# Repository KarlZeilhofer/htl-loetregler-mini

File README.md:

HTL Lötregler Mini
==================

Einfacher Regler für JBC Lötspitzen der Serie T210, T245 und T470, Weller RT-Spitzen und TS100-Spitzen sollten auch funktionieren.

Vorrangig SMD-Bauteile, Größe 3216. 
Bauteilauswahl für Handbestückung ohne SMD-Schablone optimiert

Design ist möglichst kostengünstig, speziell für Schüler-Budget. 

# Merkmale:
## Controller
* ATmega328, Kompatibel zu Arduino Nano
* 5V, 16MHz
* externe 2.5V Spannungsreferenz für ADC

## Stromversorgung
* Spannungsversorgung: 15 bis 48V, Akku oder Netzteil
* Tiefentladeschutz
* 10A Schmelzsicherung
* 48V TVS-Schutzdiode
* Ein-/Aus-Taster
* Schaltregler von Vin auf 12V und 5V
* 6.3 mm Flachsteckverbinder für die direkte Kontaktierung von 18V Makita Akkus, oder Hofer ActivEnergy Akkus mit 20 oder 40V. 

## Leistungsteil
* Highside N-Kanal MOS-FET: 80V, 10mR (geringe Verlustleistung, hohe Spannungsfestigkeit)
* zugehöriger Gatetreiber: notwendig für N-Kanal MOS-FET

## Sensorik
* Messverstärker zur Temperaturmessung der Lötspitze (24 µV/K)
* Spannungsmessung der Versorgung
* Messung der Leiterplattentemperatur
* Strommessung des Heizelements über 1mR-Shunt

## Benutzerschnittstelle
* OLED Display mit 128x32 Pixel, 23mm Diagonale
* 4 Bedientaster (Rauf, Runter, Enter, Zurück)

## Kommunikation
* Arduino USB
* AVR ISP
* Wahlweise
  * RS232
  * oder RS485 zur Kommunikation mit einem Steuerbaren Netzgerät (12, 24, 48V).

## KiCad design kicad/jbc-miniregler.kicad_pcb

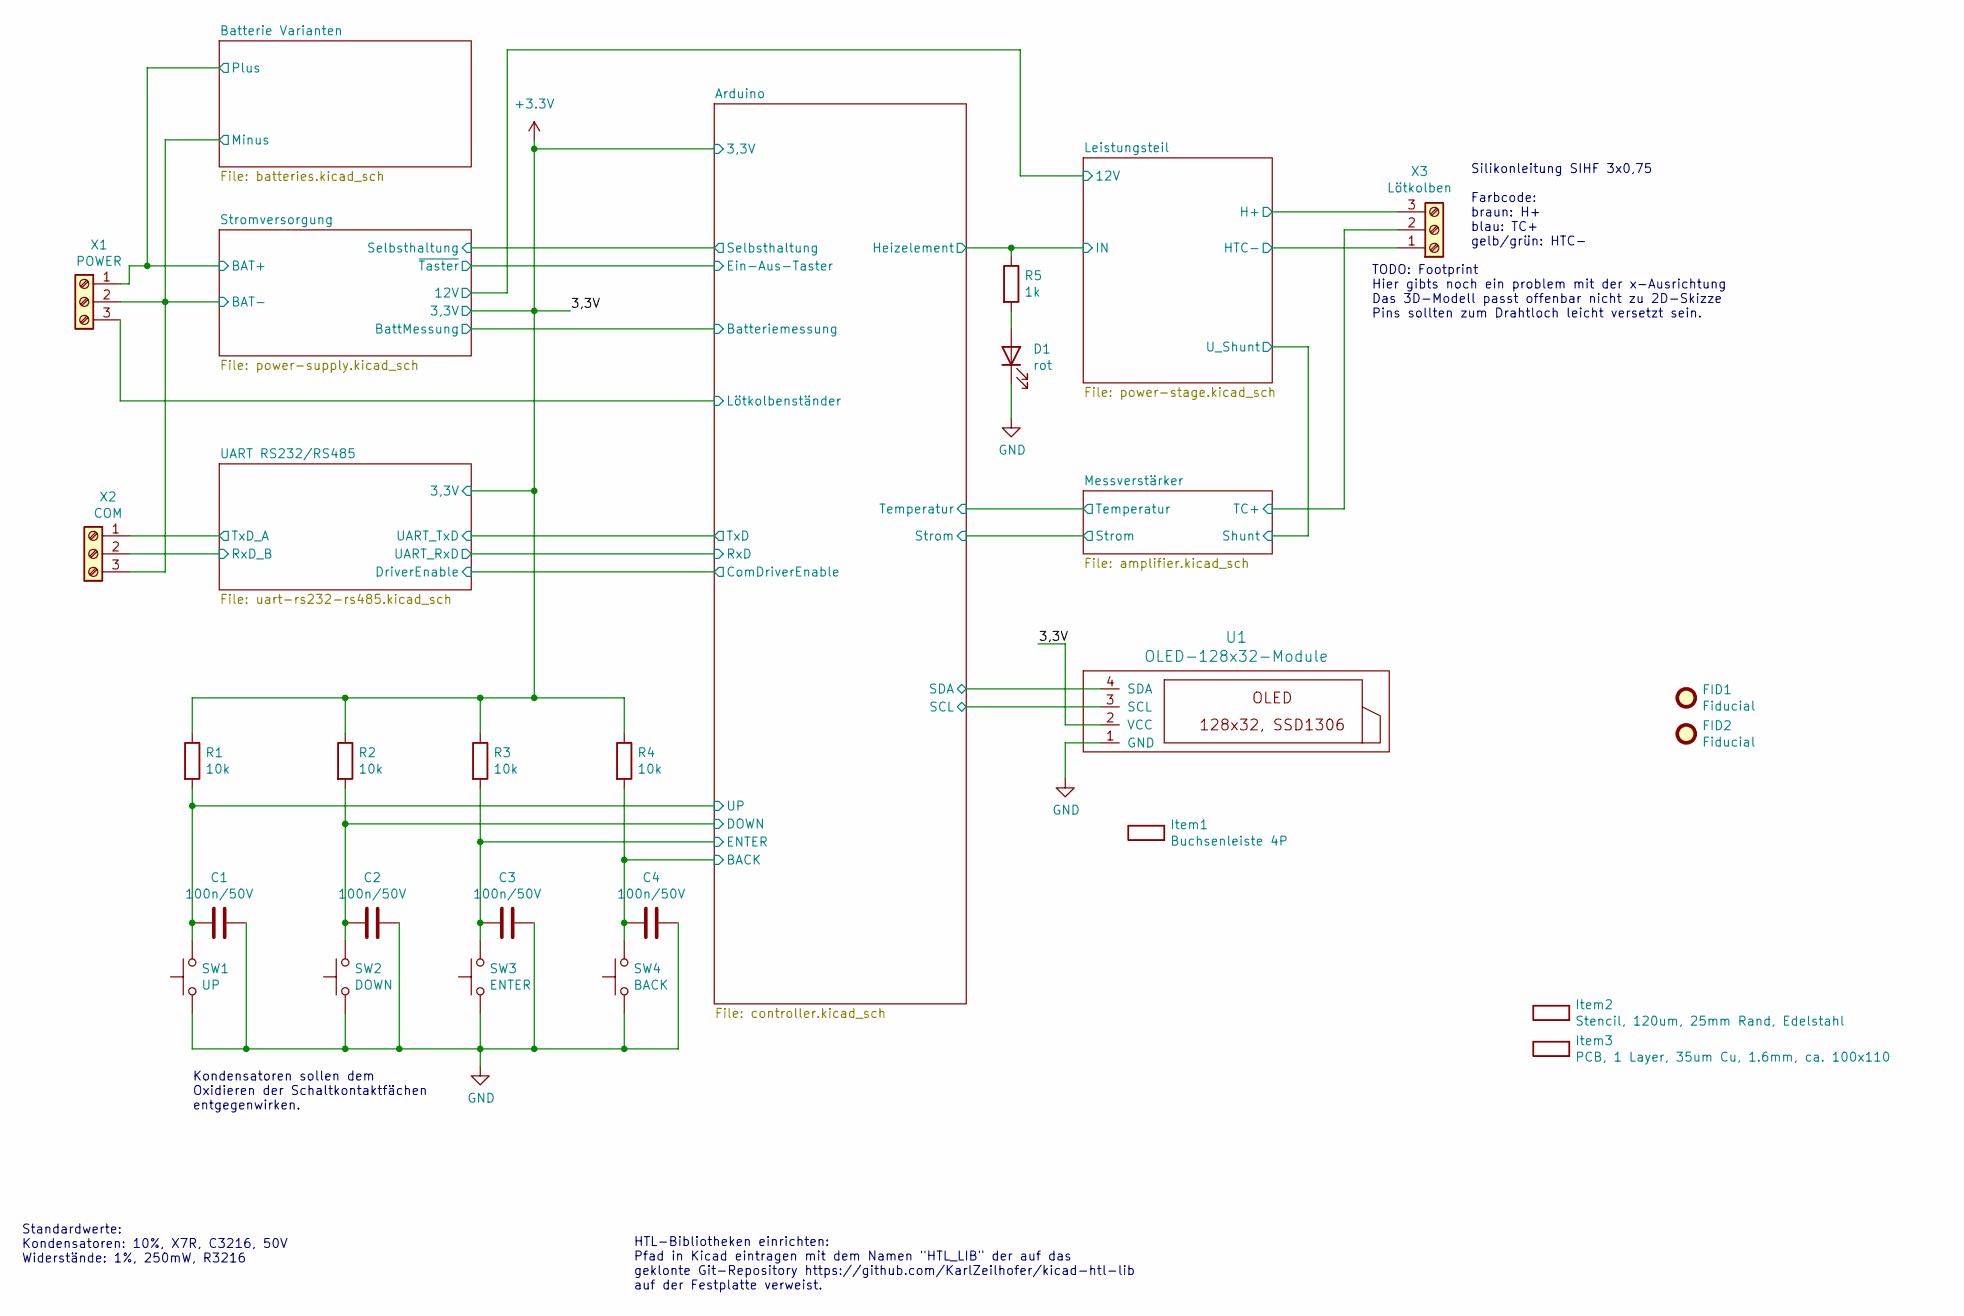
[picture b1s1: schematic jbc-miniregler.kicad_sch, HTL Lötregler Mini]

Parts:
C1, C2, C3, C4: 100n/50V; C_1206_3216Metric; ManPartNr FN31X104K500PXG
D1: rot; LED_1206_3216Metric; ManPartNr XL-3216UOC
FID1, FID2: Fiducial; paste-fiducial; ManPartNr NAP
Item1: Buchsenleiste 4P; Virtual-Item; ManPartNr A2541HWV-4P
Item2: Stencil, 120um, 25mm Rand, Edelstahl; Virtual-Item
Item3: PCB, 1 Layer, 35um Cu, 1.6mm, ca. 100x110; Virtual-Item
R1, R2, R3, R4: 10k; R_1206_3216Metric; ManPartNr RS-06K103JT
R5: 1k; R_1206_3216Metric; ManPartNr RTT03101JTP
SW1: UP; SW_Push_5.1mm_H1.5mm; ManPartNr TS-1187A-B-A-B
SW2: DOWN; SW_Push_5.1mm_H1.5mm; ManPartNr TS-1187A-B-A-B
SW3: ENTER; SW_Push_5.1mm_H1.5mm; ManPartNr TS-1187A-B-A-B
SW4: BACK; SW_Push_5.1mm_H1.5mm; ManPartNr TS-1187A-B-A-B
U1: OLED-128x32-Module; OLED-128x32
X1: POWER; Federklemme_KF142_3P_P5.08mm_C475145; ManPartNr KF142R-5.08-3P
X2: COM; Federklemme_KF142_3P_P5.08mm_C475145; ManPartNr KF142R-5.08-3P
X3: Lötkolben; Federklemme_KF142_3P_P5.08mm_C475145; ManPartNr KF142R-5.08-3P

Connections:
+3.3V: R1.1, R2.1, R3.1, R4.1, U1.2 (VCC); also elsewhere on the board
/Arduino/BACK: C4.2, R4.2, SW4.2; also elsewhere on the board
/Arduino/DOWN: C2.2, R2.2, SW2.2; also elsewhere on the board
/Arduino/ENTER: C3.2, R3.2, SW3.2; also elsewhere on the board
/Arduino/Heizelement: R5.1; also elsewhere on the board
/Arduino/Lötkolbenständer: X1.3; also elsewhere on the board
/Arduino/SCL: U1.3 (SCL); also elsewhere on the board
/Arduino/SDA: U1.4 (SDA); also elsewhere on the board
/Arduino/UP: C1.2, R1.2, SW1.2; also elsewhere on the board
/Batterie Varianten/Plus: X1.1; also elsewhere on the board
/Leistungsteil/H+: X3.3; also elsewhere on the board
/Leistungsteil/HTC-: X3.1; also elsewhere on the board
/Messverstärker/TC+: X3.2; also elsewhere on the board
/UART RS232/RS485/RxD_B: X2.2; also elsewhere on the board
/UART RS232/RS485/TxD_A: X2.1; also elsewhere on the board
GNDPWR: X1.2, X2.3; also elsewhere on the board
unnamed: D1.2 (A), R5.2

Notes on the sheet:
TODO: Footprint Hier gibts noch ein problem mit der x-Ausrichtung Das 3D-Modell passt offenbar nicht zu 2D-Skizze Pins sollten zum Drahtloch leicht versetzt sein.
Standardwerte: Kondensatoren: 10%, X7R, C3216, 50V Widerstände: 1%, 250mW, R3216
HTL-Bibliotheken einrichten: Pfad in Kicad eintragen mit dem Namen "HTL_LIB" der auf das geklonte Git-Repository https://github.com/KarlZeilhofer/kicad-htl-lib auf der Festplatte verweist.
Silikonleitung SIHF 3x0,75 Farbcode: braun: H+ blau: TC+ gelb/grün: HTC-
Kondensatoren sollen dem Oxidieren der Schaltkontaktfächen entgegenwirken.

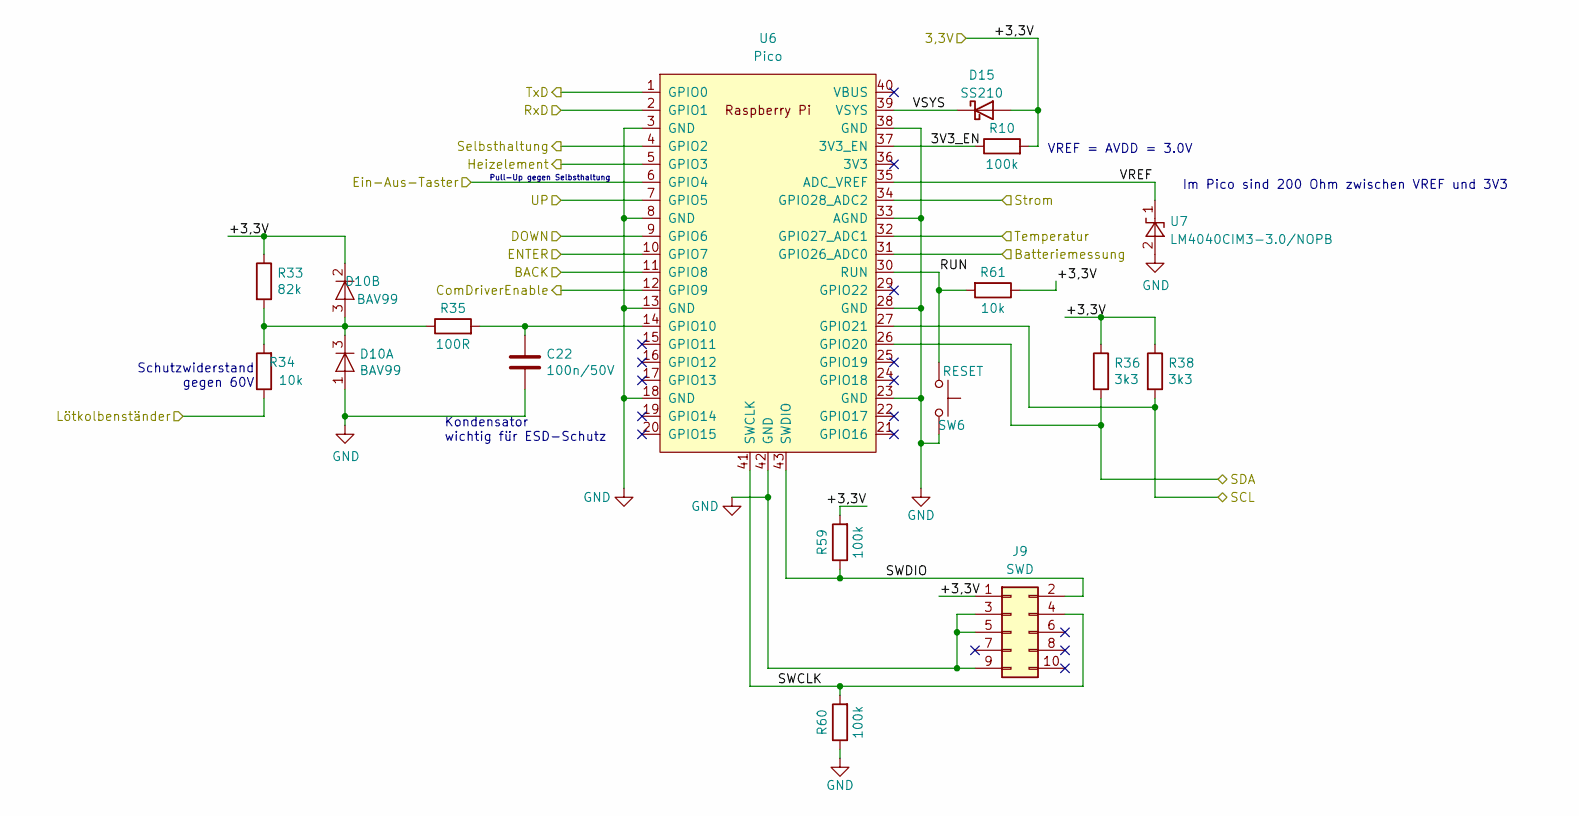
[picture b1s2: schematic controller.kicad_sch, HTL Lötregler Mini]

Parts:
C22: 100n/50V; C_1206_3216Metric; ManPartNr FN31X104K500PXG
D10: BAV99; SOT-23; ManPartNr BAV99
D15: SS210; D_SMA_wide; ManPartNr SS210A-W
J9: SWD; IDC-Header_2x05_P2.54mm_Vertical; ManPartNr C5665
R10, R59, R60: 100k; R_1206_3216Metric; ManPartNr RMC1206100K1%N
R33: 82k; R_1206_3216Metric; ManPartNr RS-06K8202FT
R34, R61: 10k; R_1206_3216Metric; ManPartNr RS-06K103JT
R35: 100R; R_1206_3216Metric; ManPartNr CR1206F100RP05Z
R36, R38: 3k3; R_1206_3216Metric; ManPartNr AC1206FR-073K3L
SW6: RESET; SW_Push_5.1mm_H1.5mm; ManPartNr TS-1187A-B-A-B
U6: Pico; RPi_Pico_SMD
U7: LM4040CIM3-3.0/NOPB; SOT-23

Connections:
+3.3V: D10.2 (K), D15.2 (A), J9.1, R10.2, R33.1, R36.1, R38.1, R59.2, R61.1; also elsewhere on the board
/Arduino/3V3_EN: R10.1, U6.37 (3V3_EN)
/Arduino/BACK: U6.11 (GPIO8); also elsewhere on the board
/Arduino/Batteriemessung: U6.31 (GPIO26_ADC0); also elsewhere on the board
/Arduino/ComDriverEnable: U6.12 (GPIO9); also elsewhere on the board
/Arduino/DOWN: U6.9 (GPIO6); also elsewhere on the board
/Arduino/ENTER: U6.10 (GPIO7); also elsewhere on the board
/Arduino/Ein-Aus-Taster: U6.6 (GPIO4); also elsewhere on the board
/Arduino/Heizelement: U6.5 (GPIO3); also elsewhere on the board
/Arduino/Lötkolbenständer: R34.1; also elsewhere on the board
/Arduino/RUN: R61.2, SW6.1, U6.30 (RUN)
/Arduino/RxD: U6.2 (GPIO1); also elsewhere on the board
/Arduino/SCL: R38.2, U6.27 (GPIO21); also elsewhere on the board
/Arduino/SDA: R36.2, U6.26 (GPIO20); also elsewhere on the board
/Arduino/SWCLK: J9.4, R60.2, U6.41 (SWCLK)
/Arduino/SWDIO: J9.2, R59.1, U6.43 (SWDIO)
/Arduino/Selbsthaltung: U6.4 (GPIO2); also elsewhere on the board
/Arduino/Strom: U6.34 (GPIO28_ADC2); also elsewhere on the board
/Arduino/Temperatur: U6.32 (GPIO27_ADC1); also elsewhere on the board
/Arduino/TxD: U6.1 (GPIO0); also elsewhere on the board
/Arduino/UP: U6.7 (GPIO5); also elsewhere on the board
/Arduino/VREF: U6.35 (ADC_VREF), U7.1 (K)
/Arduino/VSYS: D15.1 (K), U6.39 (VSYS)
unnamed: C22.1, R35.2, U6.14 (GPIO10)
unnamed: D10.3 (A), R33.2, R34.2, R35.1

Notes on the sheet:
VREF = AVDD = 3.0V
Pull-Up gegen Selbsthaltung
Im Pico sind 200 Ohm zwischen VREF und 3V3
Kondensator wichtig für ESD-Schutz
Schutzwiderstand gegen 60V

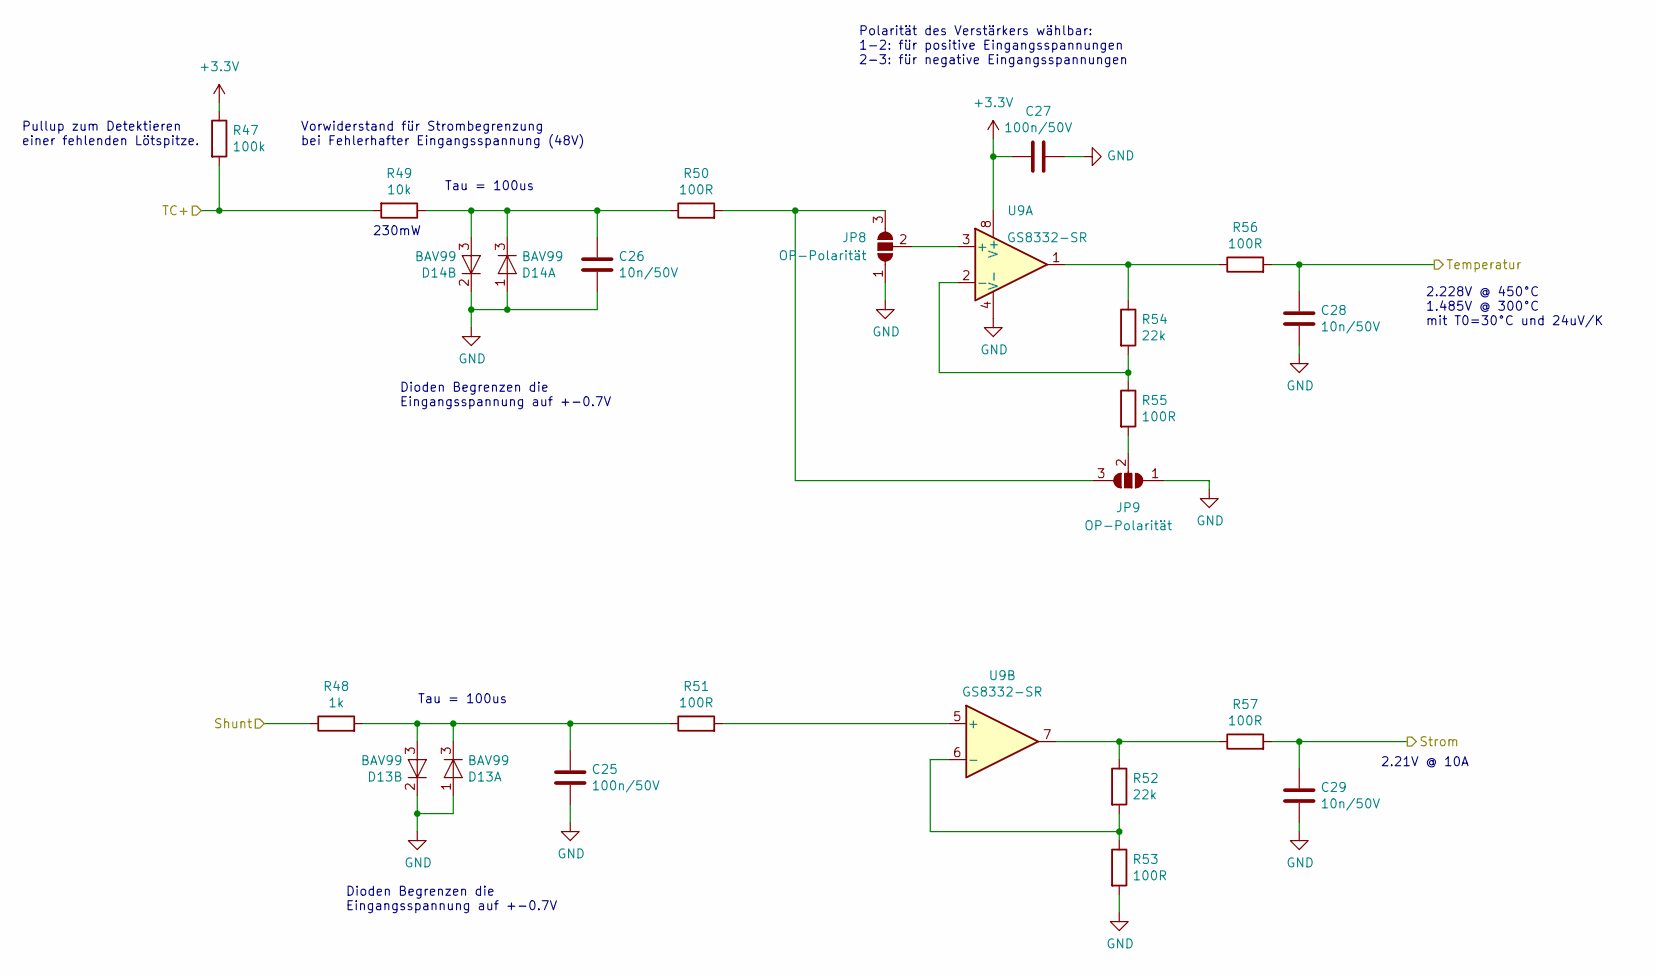
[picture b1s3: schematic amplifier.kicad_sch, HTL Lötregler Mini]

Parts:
C25, C27: 100n/50V; C_1206_3216Metric; ManPartNr FN31X104K500PXG
C26, C28, C29: 10n/50V; C_1206_3216Metric; ManPartNr FN31X103K500PXG
D13, D14: BAV99; SOT-23; ManPartNr BAV99
JP8, JP9: OP-Polarität; SolderJumper-3_P2.0mm_Open_TrianglePad1.0x1.5mm_NumberLabels; ManPartNr NAP
R47: 100k; R_1206_3216Metric; ManPartNr RMC1206100K1%N
R48: 1k; R_1206_3216Metric; ManPartNr RTT03101JTP
R49: 10k; R_1206_3216Metric; ManPartNr RS-06K103JT
R50, R51, R53, R55, R56, R57: 100R; R_1206_3216Metric; ManPartNr CR1206F100RP05Z
R52, R54: 22k; R_1206_3216Metric
U9: GS8332-SR; SOIC-8_3.9x4.9mm_P1.27mm; ManPartNr GS8332-SR

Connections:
+3.3V: C27.2, R47.1, U9.8 (V+); also elsewhere on the board
/Arduino/Strom: C29.1, R57.2; also elsewhere on the board
/Arduino/Temperatur: C28.1, R56.2; also elsewhere on the board
/Leistungsteil/U_Shunt: R48.1; also elsewhere on the board
/Messverstärker/TC+: R47.2, R49.2; also elsewhere on the board
unnamed: C25.2, D13.3 (K), R48.2, R51.1
unnamed: C26.1, D14.3 (K), R49.1, R50.1
unnamed: JP8.2 (C), U9.3 (+)
unnamed: JP8.3 (B), JP9.3 (B), R50.2
unnamed: JP9.2 (C), R55.2
unnamed: R51.2, U9.5 (+)
unnamed: R52.1, R57.1, U9.7
unnamed: R52.2, R53.1, U9.6 (-)
unnamed: R54.1, R56.1, U9.1
unnamed: R54.2, R55.1, U9.2 (-)

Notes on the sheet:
Dioden Begrenzen die Eingangsspannung auf +-0.7V
230mW
Tau = 100us
Vorwiderstand für Strombegrenzung bei Fehlerhafter Eingangsspannung (48V)
Pullup zum Detektieren einer fehlenden Lötspitze.
Polarität des Verstärkers wählbar: 1-2: für positive Eingangsspannungen 2-3: für negative Eingangsspannungen
2.228V @ 450°C 1.485V @ 300°C mit T0=30°C und 24uV/K
2.21V @ 10A

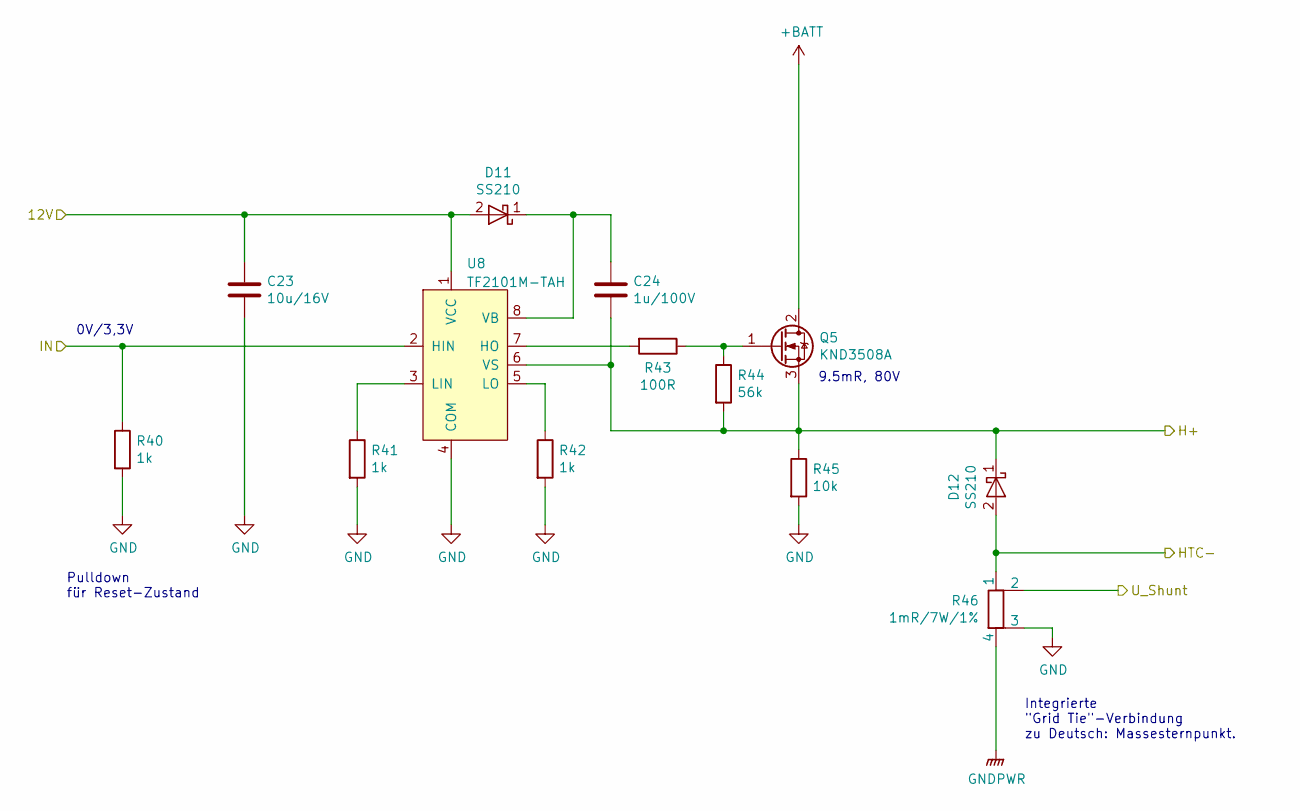
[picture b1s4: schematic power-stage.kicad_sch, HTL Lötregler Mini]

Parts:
C23: 10u/16V; C_1206_3216Metric; ManPartNr CL31B106KOHNNNE
C24: 1u/100V; C_1206_3216Metric; ManPartNr CC1206KKX7R0BB105
D11, D12: SS210; D_SMA_wide; ManPartNr SS210A-W
Q5: KND3508A; TO-252-2; ManPartNr KND3508A
R40, R41, R42: 1k; R_1206_3216Metric; ManPartNr RTT03101JTP
R43: 100R; R_1206_3216Metric; ManPartNr CR1206F100RP05Z
R44: 56k; R_1206_3216Metric
R45: 10k; R_1206_3216Metric; ManPartNr RS-06K103JT
R46: 1mR/7W/1%; Shunt-15.2x7.6mm; ManPartNr HoLRS1575-1mR-1%
U8: TF2101M-TAH; SOIC-8_3.9x4.9mm_P1.27mm; ManPartNr -nicht mehr aktuell?

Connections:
+BATT: Q5.2 (D); also elsewhere on the board
/Arduino/Heizelement: R40.1, U8.2 (HIN); also elsewhere on the board
/Leistungsteil/12V: C23.1, D11.2 (A), U8.1 (VCC); also elsewhere on the board
/Leistungsteil/H+: C24.2, D12.1 (K), Q5.3 (S), R44.2, R45.1, U8.6 (VS); also elsewhere on the board
/Leistungsteil/HTC-: D12.2 (A), R46.1; also elsewhere on the board
/Leistungsteil/U_Shunt: R46.2; also elsewhere on the board
GNDPWR: R46.4; also elsewhere on the board
unnamed: C24.1, D11.1 (K), U8.8 (VB)
unnamed: Q5.1 (G), R43.1, R44.1
unnamed: R41.1, U8.3 (LIN)
unnamed: R42.1, U8.5 (LO)
unnamed: R43.2, U8.7 (HO)

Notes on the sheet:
Integrierte "Grid Tie"-Verbindung zu Deutsch: Massesternpunkt.
9.5mR, 80V
Pulldown für Reset-Zustand
0V/3,3V

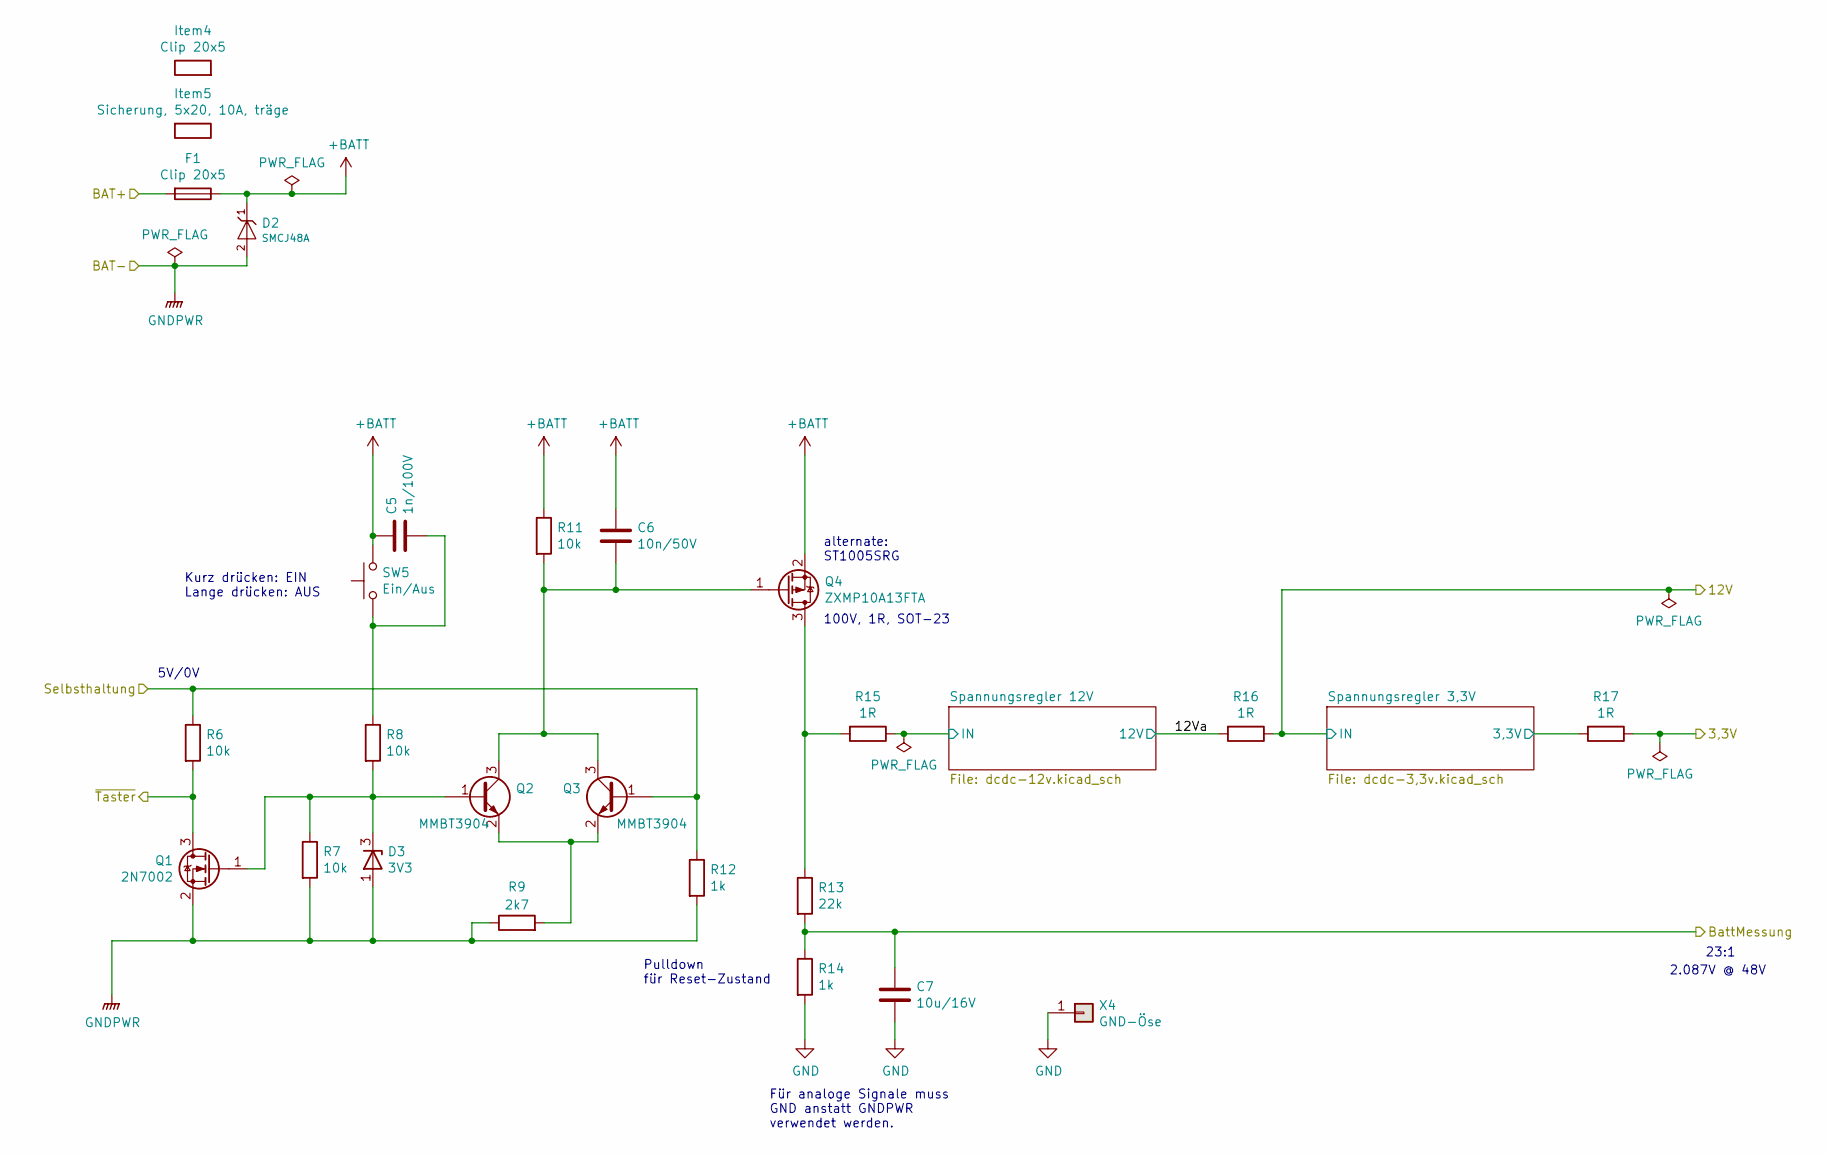
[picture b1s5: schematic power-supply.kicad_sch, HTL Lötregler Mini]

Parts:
C5: 1n/100V; C_1206_3216Metric; ManPartNr C1206X102K101T
C6: 10n/50V; C_1206_3216Metric; ManPartNr FN31X103K500PXG
C7: 10u/16V; C_1206_3216Metric; ManPartNr CL31B106KOHNNNE
D2: SMCJ48A; D_SMC; ManPartNr SMCJ48A/TR13
D3: 3V3; SOT-23; ManPartNr BZX84-C3V3,235
F1: Clip 20x5; fuse-clip_20x5mm; ManPartNr LS-502
Item4: Clip 20x5; Virtual-Item; ManPartNr LS-502
Item5: Sicherung, 5x20, 10A, träge; Virtual-Item; ManPartNr 0618010.MXP
Q1: 2N7002; SOT-23; ManPartNr 2N7002
Q2, Q3: MMBT3904; SOT-23; ManPartNr MMBT3904
Q4: ZXMP10A13FTA; SOT-23; ManPartNr ZXMP10A13FTA
R6, R7, R8, R11: 10k; R_1206_3216Metric; ManPartNr RS-06K103JT
R9: 2k7; R_1206_3216Metric; ManPartNr RS-06K2701FT
R12, R14: 1k; R_1206_3216Metric; ManPartNr RTT03101JTP
R13: 22k; R_1206_3216Metric
R15, R16, R17: 1R; R_1206_3216Metric; ManPartNr 1206W4F100KT5E
SW5: Ein/Aus; SW_Push_5.1mm_H1.5mm; ManPartNr TS-1187A-B-A-B
X4: GND-Öse; Keystone_5016; ManPartNr 5016

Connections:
+3.3V: R17.1; also elsewhere on the board
+BATT: C5.1, C6.1, D2.1 (K), F1.1, Q4.2 (S), R11.1, SW5.2; also elsewhere on the board
/Arduino/Batteriemessung: C7.1, R13.2, R14.1; also elsewhere on the board
/Arduino/Ein-Aus-Taster: Q1.3 (D), R6.2; also elsewhere on the board
/Arduino/Selbsthaltung: Q3.1 (B), R6.1, R12.1; also elsewhere on the board
/Batterie Varianten/Plus: F1.2; also elsewhere on the board
/Leistungsteil/12V: R16.1; also elsewhere on the board
/Stromversorgung/12Va: R16.2; also elsewhere on the board
/Stromversorgung/Spannungsregler 3,3V/3,3V: R17.2; also elsewhere on the board
/Stromversorgung/Spannungsregler 12V/IN: R15.1; also elsewhere on the board
GNDPWR: D2.2 (A), D3.1 (A), Q1.2 (S), R7.2, R9.1, R12.2; also elsewhere on the board
unnamed: C5.2, R8.1, SW5.1
unnamed: C6.2, Q2.3 (C), Q3.3 (C), Q4.1 (G), R11.2
unnamed: D3.3 (K), Q1.1 (G), Q2.1 (B), R7.1, R8.2
unnamed: Q2.2 (E), Q3.2 (E), R9.2
unnamed: Q4.3 (D), R13.1, R15.2

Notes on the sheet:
Pulldown für Reset-Zustand
23:1
100V, 1R, SOT-23
2.087V @ 48V
Kurz drücken: EIN Lange drücken: AUS
Für analoge Signale muss GND anstatt GNDPWR verwendet werden.
alternate: ST1005SRG
5V/0V

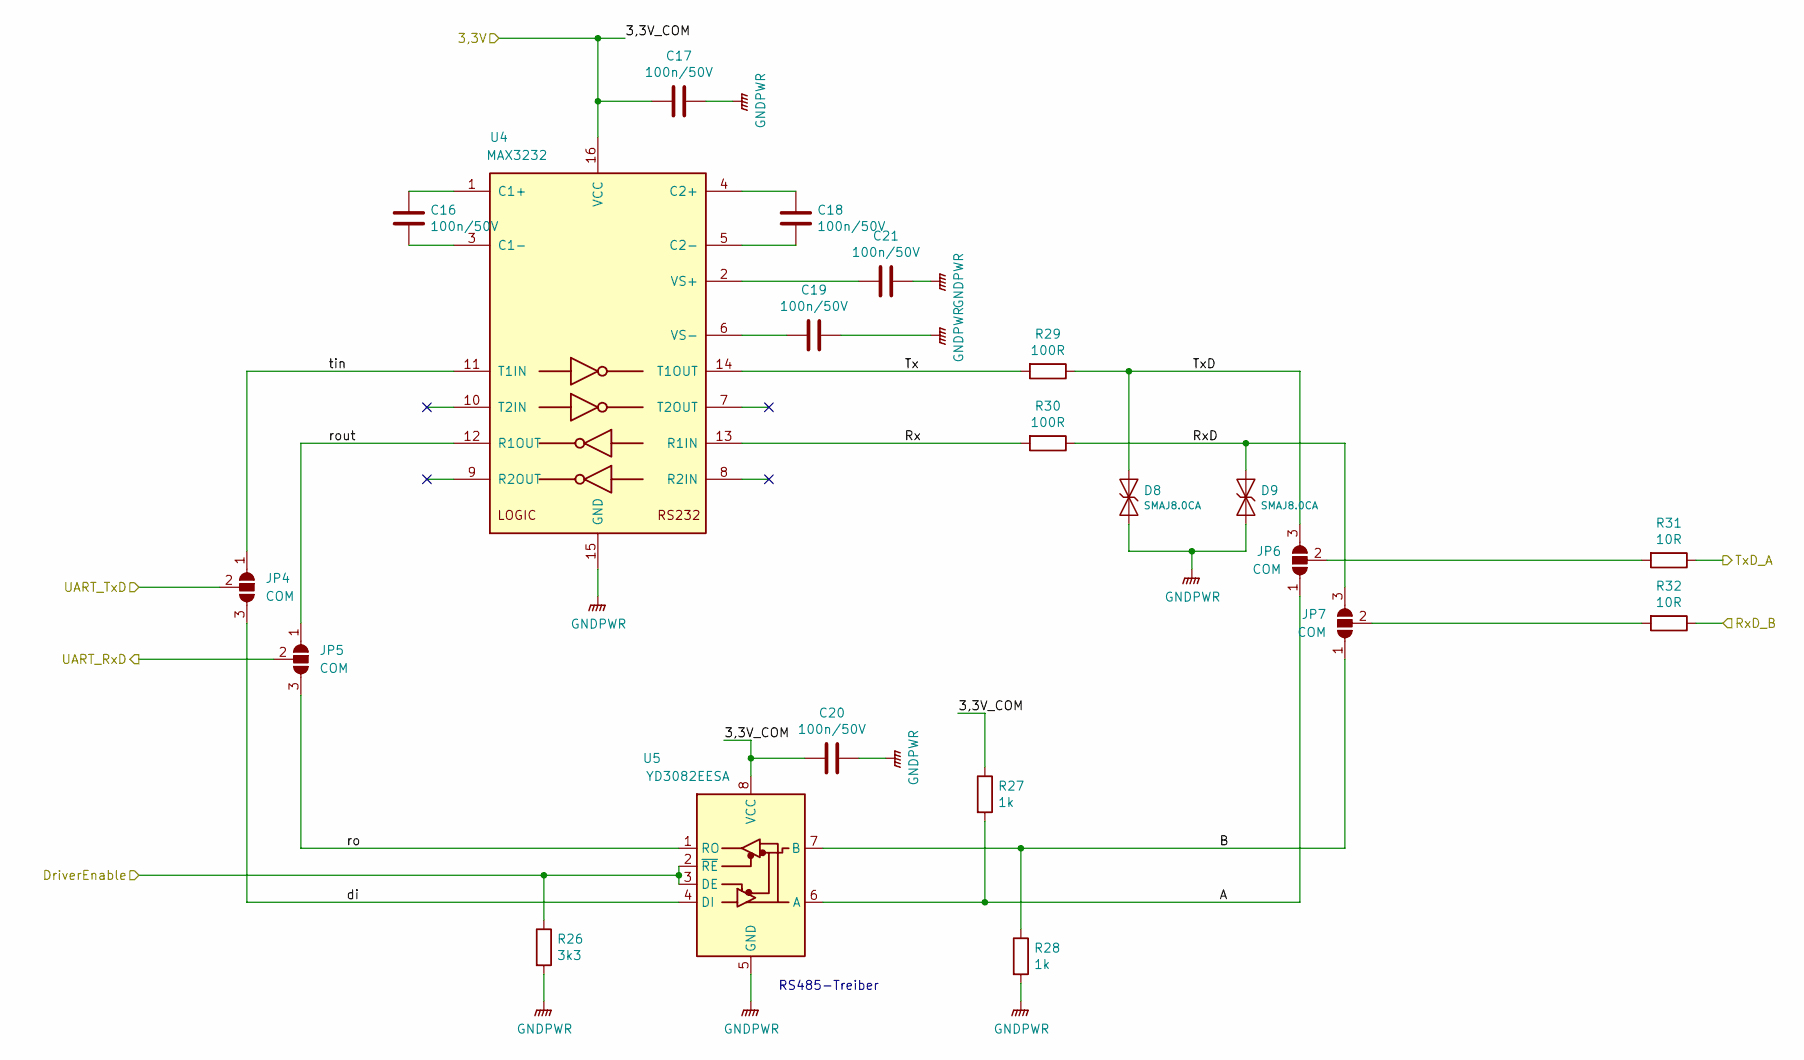
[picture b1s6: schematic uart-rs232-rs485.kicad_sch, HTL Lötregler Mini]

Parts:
C16, C17, C18, C19, C20, C21: 100n/50V; C_1206_3216Metric; ManPartNr FN31X104K500PXG
D8, D9: SMAJ8.0CA; D_SMA; ManPartNr SMAJ8.0CA
JP4, JP5, JP6, JP7: COM; SolderJumper-3_P2.0mm_Open_TrianglePad1.0x1.5mm_NumberLabels; ManPartNr NAP
R26: 3k3; R_1206_3216Metric; ManPartNr AC1206FR-073K3L
R27, R28: 1k; R_1206_3216Metric; ManPartNr RTT03101JTP
R29, R30: 100R; R_1206_3216Metric; ManPartNr CR1206F100RP05Z
R31, R32: 10R; R_1206_3216Metric
U4: MAX3232; SOIC-16_3.9x9.9mm_P1.27mm; ManPartNr MAX3232EIM/TR
U5: YD3082EESA; SOIC-8_3.9x4.9mm_P1.27mm; ManPartNr YD3082EESA

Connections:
+3.3V: C17.2, C20.2, R27.1, U4.16 (VCC), U5.8 (VCC); also elsewhere on the board
/Arduino/ComDriverEnable: R26.1, U5.2 (~RE), U5.3 (DE); also elsewhere on the board
/Arduino/RxD: JP5.2 (C); also elsewhere on the board
/Arduino/TxD: JP4.2 (C); also elsewhere on the board
/UART RS232/RS485/A: JP6.1 (A), R27.2, U5.6 (A)
/UART RS232/RS485/B: JP7.1 (A), R28.1, U5.7 (B)
/UART RS232/RS485/Rx: R30.2, U4.13 (R1IN)
/UART RS232/RS485/RxD: D9.1 (A), JP7.3 (B), R30.1
/UART RS232/RS485/RxD_B: R32.1; also elsewhere on the board
/UART RS232/RS485/Tx: R29.2, U4.14 (T1OUT)
/UART RS232/RS485/TxD: D8.1 (A), JP6.3 (B), R29.1
/UART RS232/RS485/TxD_A: R31.1; also elsewhere on the board
/UART RS232/RS485/di: JP4.3 (B), U5.4 (DI)
/UART RS232/RS485/ro: JP5.3 (B), U5.1 (RO)
/UART RS232/RS485/rout: JP5.1 (A), U4.12 (R1OUT)
/UART RS232/RS485/tin: JP4.1 (A), U4.11 (T1IN)
GNDPWR: C17.1, C19.1, C20.1, C21.1, D8.2 (K), D9.2 (K), R26.2, R28.2, U4.15 (GND), U5.5 (GND); also elsewhere on the board
unnamed: C16.1, U4.1 (C1+)
unnamed: C16.2, U4.3 (C1-)
unnamed: C18.1, U4.4 (C2+)
unnamed: C18.2, U4.5 (C2-)
unnamed: C19.2, U4.6 (VS-)
unnamed: C21.2, U4.2 (VS+)
unnamed: JP6.2 (C), R31.2
unnamed: JP7.2 (C), R32.2

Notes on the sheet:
RS485-Treiber

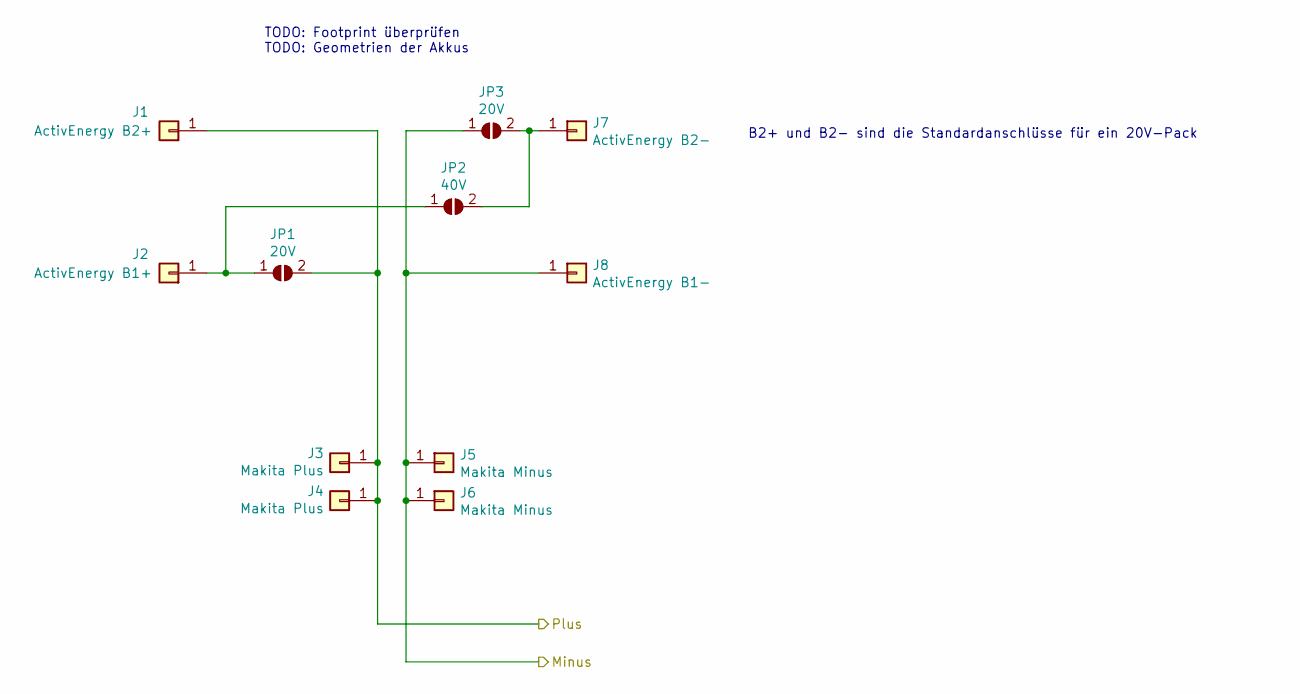
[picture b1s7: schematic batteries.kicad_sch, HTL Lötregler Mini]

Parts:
J1: ActivEnergy B2+; Faston_Tab_6.3mm_vertical; ManPartNr 03866.A68
J2: ActivEnergy B1+; Faston_Tab_6.3mm_vertical; ManPartNr 03866.A68
J3, J4: Makita Plus; Faston_Tab_6.3mm_vertical; ManPartNr 03866.A68
J5, J6: Makita Minus; Faston_Tab_6.3mm_vertical; ManPartNr 03866.A68
J7: ActivEnergy B2-; Faston_Tab_6.3mm_vertical; ManPartNr 03866.A68
J8: ActivEnergy B1-; Faston_Tab_6.3mm_vertical; ManPartNr 03866.A68
JP1, JP3: 20V; SolderJumper-2_2.2x8mm_Open; ManPartNr NAP
JP2: 40V; SolderJumper-2_2.2x8mm_Open; ManPartNr NAP

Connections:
/Batterie Varianten/Plus: J1.1, J3.1, J4.1, JP1.2 (B); also elsewhere on the board
GNDPWR: J5.1, J6.1, J8.1, JP3.1 (A); also elsewhere on the board
unnamed: J2.1, JP1.1 (A), JP2.1 (A)
unnamed: J7.1, JP2.2 (B), JP3.2 (B)

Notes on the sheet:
TODO: Footprint überprüfen TODO: Geometrien der Akkus
B2+ und B2- sind die Standardanschlüsse für ein 20V-Pack

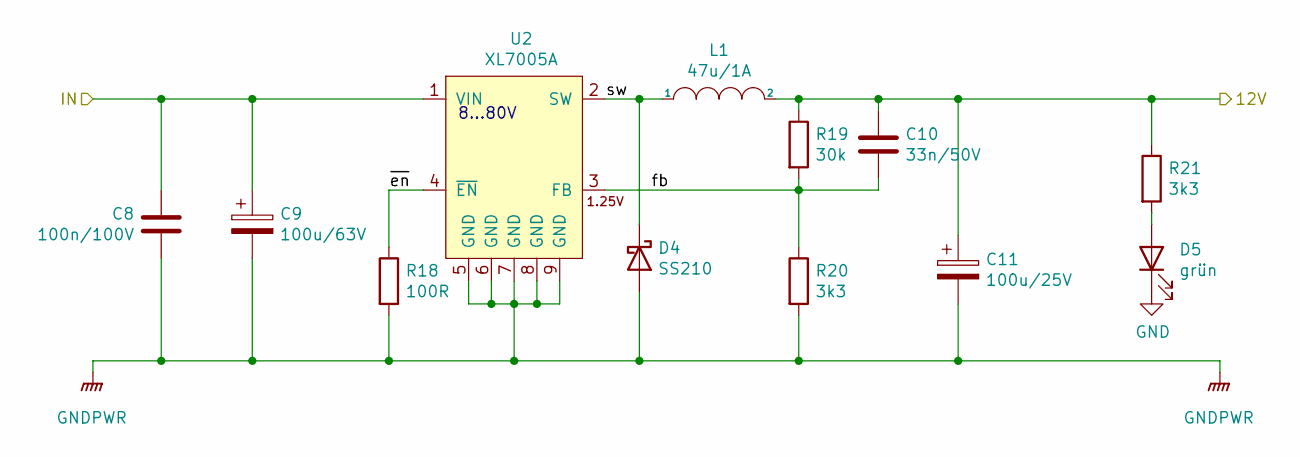
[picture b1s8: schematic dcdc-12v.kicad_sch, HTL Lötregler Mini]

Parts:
C8: 100n/100V; C_1206_3216Metric; ManPartNr CL31B104KCFNNNE
C9: 100u/63V; CP_Elec_8x10; ManPartNr VKMD1001J101MV
C10: 33n/50V; C_1206_3216Metric; ManPartNr TCC1206X7R333K500DT
C11: 100u/25V; CP_Elec_6.3x5.9; ManPartNr SVZ1EM101E06E00RAXXX
D4: SS210; D_SMA_wide; ManPartNr SS210A-W
D5: grün; LED_1206_3216Metric; ManPartNr XL-3216UGC
L1: 47u/1A; L_7.3x7.3_H4.5_C216198; ManPartNr SLH0704S470MTT
R18: 100R; R_1206_3216Metric; ManPartNr CR1206F100RP05Z
R19: 30k; R_1206_3216Metric; ManPartNr RC1206FR-0730KL
R20, R21: 3k3; R_1206_3216Metric; ManPartNr AC1206FR-073K3L
U2: XL7005A; SOIC-8-1EP_3.9x4.9mm_P1.27mm_EP2.514x3.2mm_ThermalVias; ManPartNr XL7005A

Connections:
/Stromversorgung/12Va: C10.1, C11.1, L1.2, R19.1, R21.1; also elsewhere on the board
/Stromversorgung/Spannungsregler 12V/IN: C8.1, C9.1, U2.1 (VIN); also elsewhere on the board
/Stromversorgung/Spannungsregler 12V/fb: C10.2, R19.2, R20.1, U2.3 (FB)
/Stromversorgung/Spannungsregler 12V/sw: D4.1 (K), L1.1, U2.2 (SW)
/Stromversorgung/Spannungsregler 12V/~en: R18.1, U2.4 (~EN)
GNDPWR: C8.2, C9.2, C11.2, D4.2 (A), R18.2, R20.2, U2.5 (GND), U2.6 (GND), U2.7 (GND), U2.8 (GND), U2.9 (GND); also elsewhere on the board
unnamed: D5.2 (A), R21.2

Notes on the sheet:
8...80V

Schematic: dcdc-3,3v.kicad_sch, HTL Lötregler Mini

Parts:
C12: 100n/100V; C_1206_3216Metric; ManPartNr CL31B104KCFNNNE
C13, C15: 100u/25V; CP_Elec_6.3x5.9; ManPartNr SVZ1EM101E06E00RAXXX
C14: 33n/50V; C_1206_3216Metric; ManPartNr TCC1206X7R333K500DT
D6: SS210; D_SMA_wide; ManPartNr SS210A-W
D7: grün; LED_1206_3216Metric; ManPartNr XL-3216UGC
L2: 47u/1A; L_7.3x7.3_H4.5_C216198; ManPartNr SLH0704S470MTT
R22: 100R; R_1206_3216Metric; ManPartNr CR1206F100RP05Z
R23: 10k; R_1206_3216Metric; ManPartNr RS-06K103JT
R24: 6k2; R_1206_3216Metric; ManPartNr RS-06K6191FT
R25: 680R; R_1206_3216Metric; ManPartNr RS-06K681JT
U3: XL7005A; SOIC-8-1EP_3.9x4.9mm_P1.27mm_EP2.514x3.2mm_ThermalVias; ManPartNr XL7005A

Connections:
/Leistungsteil/12V: C12.1, C13.1, U3.1 (VIN); also elsewhere on the board
/Stromversorgung/Spannungsregler 3,3V/3,3V: C14.1, C15.1, L2.2, R23.1, R25.1; also elsewhere on the board
/Stromversorgung/Spannungsregler 3,3V/fb: C14.2, R23.2, R24.1, U3.3 (FB)
/Stromversorgung/Spannungsregler 3,3V/sw: D6.1 (K), L2.1, U3.2 (SW)
/Stromversorgung/Spannungsregler 3,3V/~en: R22.1, U3.4 (~EN)
GNDPWR: C12.2, C13.2, C15.2, D6.2 (A), R22.2, R24.2, U3.5 (GND), U3.6 (GND), U3.7 (GND), U3.8 (GND), U3.9 (GND); also elsewhere on the board
unnamed: D7.2 (A), R25.2

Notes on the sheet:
8...80V

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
